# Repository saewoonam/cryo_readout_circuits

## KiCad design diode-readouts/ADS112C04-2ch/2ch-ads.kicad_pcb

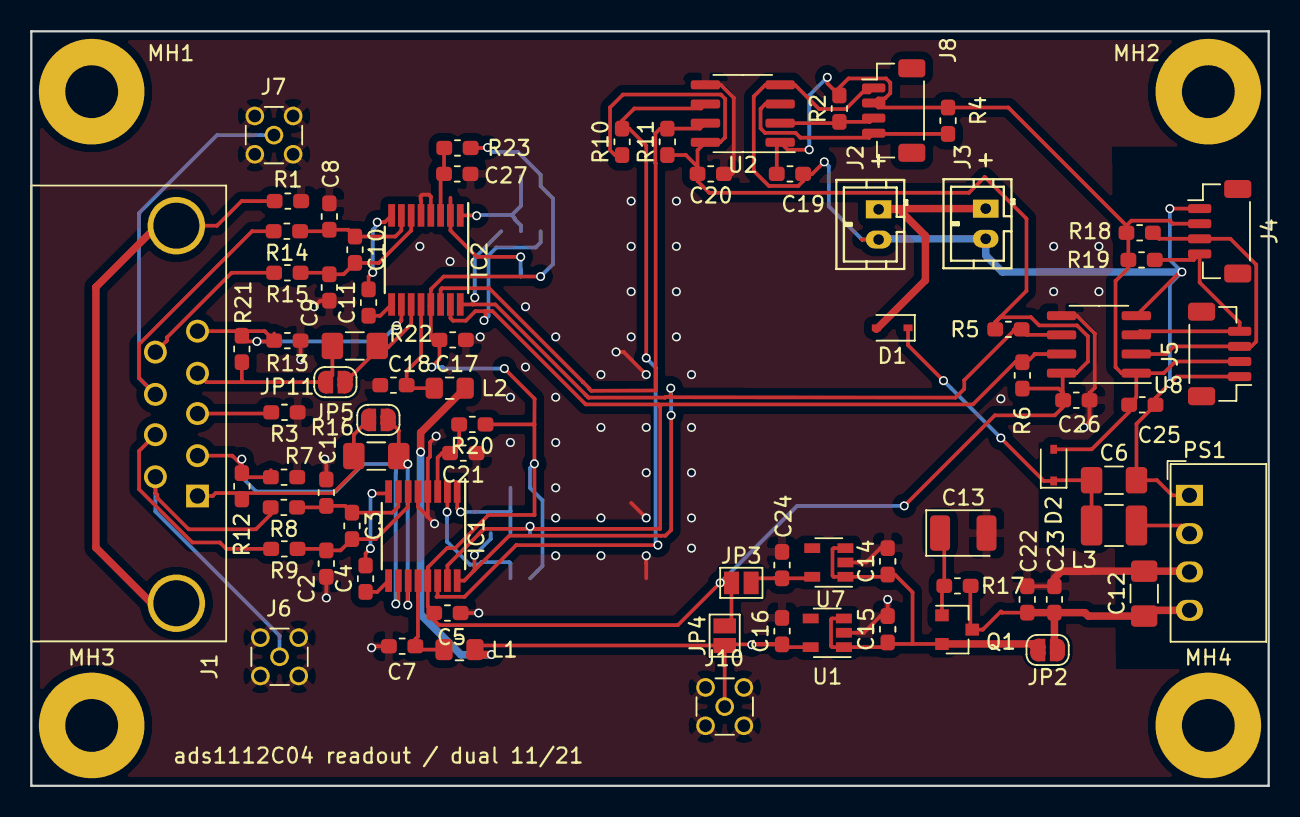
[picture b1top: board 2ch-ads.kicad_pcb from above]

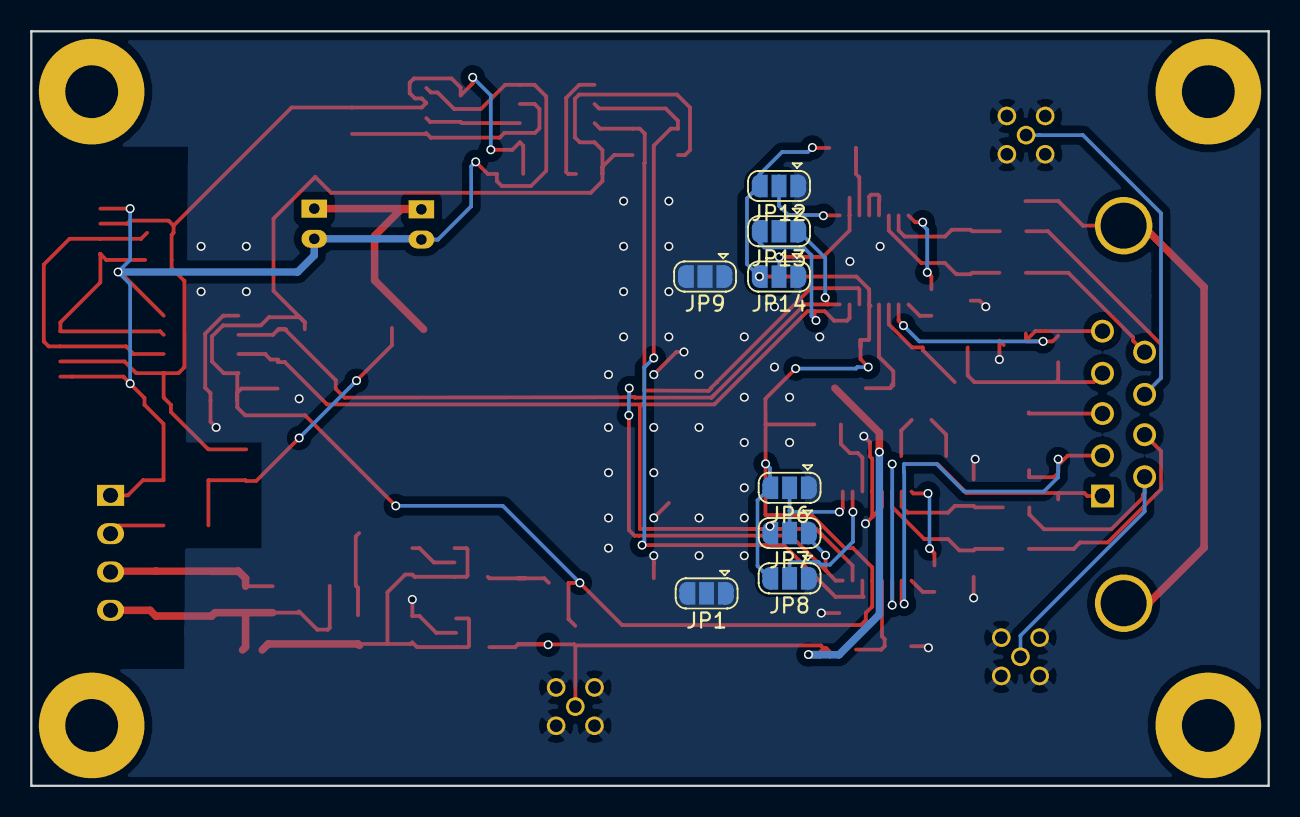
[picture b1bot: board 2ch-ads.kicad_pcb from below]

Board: 2 copper layers, 82.0 x 50.0 mm, 89 parts (8 on the bottom side), 48 nets.

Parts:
C1, C2, C4, C5, C7, C8, C9, C11, C17, C18, C19, C20, C21, C22, C25, C26, C27: 100nF; C_0603_1608Metric_Pad1.05x0.95mm_HandSolder
C3, C10, C14, C15, C16, C24: 1uF; C_0603_1608Metric_Pad1.05x0.95mm_HandSolder
C6: 4.7uF_1206_50V; C_1206_3216Metric_Pad1.42x1.75mm_HandSolder
C12: 10uF_1206_50V; C_1206_3216Metric_Pad1.42x1.75mm_HandSolder
C13: 100uF; CP_EIA-3528-12_Kemet-T
C23: 10nF; C_0603_1608Metric_Pad1.05x0.95mm_HandSolder
D1, D2: BAT60B; D_SOD-323
IC1, IC2: ADS112C04IPWR; TSSOP-16_4.4x5mm_P0.65mm
J1: DB9_Female_MountingHoles; DB9_ASSMANN
J2, J3: Conn_01x02; JST_lipo_adafruit
J4, J5, J8: A1001WV-S-04P; JST_SH_BM04B-SRSS-TB_1x04-1MP_P1.00mm_Vertical
J6, J7, J10: MMCX; MMCX_JLC
JP1, JP6, JP7, JP8, JP9, JP12, JP13, JP14: Jumper_3_Open; SolderJumper-3_P1.3mm_Open_RoundedPad1.0x1.5mm
JP2: Jumper_2_Open; SolderJumper-2_P1.3mm_Open_RoundedPad1.0x1.5mm
JP3, JP4: Jumper_NO_Small; SolderJumper-2_P1.3mm_Open_Pad1.0x1.5mm
JP5, JP11: Jumper; SolderJumper-2_P1.3mm_Open_RoundedPad1.0x1.5mm
L1, L2: MMZ2012Y202B; L_0805_2012Metric_Pad1.15x1.40mm_HandSolder
L3: 6.8uH; L_1210_3225Metric_Pad1.42x2.65mm_HandSolder
MH1, MH2, MH3, MH4: MountingHole; MountingHole_3.5mm_Pad
PS1: B0305S-1WR2; Converter_DCDC_muRata_CRE1xxxxxx3C_THT
Q1: BC847C; SOT-23
R1, R3: dnf; R_0603_1608Metric_Pad1.05x0.95mm_HandSolder
R2, R4, R5, R6, R10, R11, R18, R19: 4.7K; R_0603_1608Metric_Pad1.05x0.95mm_HandSolder
R7, R13: 10K 0.1%; R_0603_1608Metric_Pad1.05x0.95mm_HandSolder
R8, R9, R14, R15: 100K; R_0603_1608Metric_Pad1.05x0.95mm_HandSolder
R12, R21: R; R_0603_1608Metric_Pad1.05x0.95mm_HandSolder
R16, R22: 1M_0.1%; R_1206_3216Metric_Pad1.42x1.75mm_HandSolder
R17, R20, R23: 1K; R_0603_1608Metric_Pad1.05x0.95mm_HandSolder
U1, U7: LP5907MFX-3.3; SOT-23-5
U2: ADUM1250; SOIC-8_3.9x4.9mm_P1.27mm
U8: ISO1541; SOIC-8_3.9x4.9mm_P1.27mm

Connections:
/Channel0/A0: IC1.1, JP6.2, JP7.2
/Channel0/A1: IC1.2, JP1.2, JP8.2
/Channel0/AIN0: IC1.11, JP5.2, R16.1
/Channel0/I+: J1.1, JP5.1, R12.1, R16.2
/Channel0/I-: IC1.10, J1.2, R7.1, R12.2
/Channel0/V+: J1.6, J6.1, R8.2
/Channel0/V-: J1.7, R9.2
/Channel0/Vpower: C7.2, IC1.12, L1.2
/Channel1/A0: IC2.1, JP12.2, JP13.2
/Channel1/A1: IC2.2, JP9.2, JP14.2
/Channel1/AIN0: IC2.11, JP11.2, R22.1
/Channel1/I+: J1.4, JP11.1, R21.1, R22.2
/Channel1/I-: IC2.10, J1.5, R13.1, R21.2
/Channel1/V+: J1.8, J7.1, R14.2
/Channel1/V-: J1.9, R15.2
/Channel1/Vpower: C18.2, IC2.12, L2.2
/Sheet605654E7/i2c_power: C6.1, D1.1, D2.1, L3.2
/Sheet6128984A/gpio0: IC1.14, R10.2, U2.6
/Sheet6128984A/gpio1: IC2.14, R11.2, U2.7
/analog: C16.1, J10.1, JP4.1, L1.1, L2.1, U1.5
/scl: IC1.16, IC2.16, JP1.1, JP7.1, JP9.1, JP13.1, R5.2, U8.6
/sda: IC1.15, IC2.15, JP1.3, JP7.3, JP9.3, JP13.3, R6.2, U8.7
GND: C1.1, C2.2, C5.2, C7.1, C8.1, C9.2, C12.2, C13.2, C14.2, C15.2, C16.2, C17.2, C18.1, C20.1, C21.1, C22.1, C23.1, C24.2, C26.1, C27.1, IC1.4, IC1.5, IC2.4, IC2.5, J6.2, J7.2, J10.2, JP6.1, JP8.1, JP12.1, JP14.1, PS1.3, R1.2, R3.1, R7.2, R13.2, U1.2, U2.5, U7.2, U8.5
GNDPWR: C6.2, C19.2, C25.2, J2.2, J3.2, J4.1, J5.1, J8.1, PS1.1, U2.4, U8.4
unnamed: C1.2, C3.1, IC1.7, R8.1
unnamed: C2.1, C3.2, IC1.6, R9.1
unnamed: C4.1, IC1.9
unnamed: C4.2, IC1.8
unnamed: C8.2, C10.1, IC2.7, R14.1
unnamed: C9.1, C10.2, IC2.6, R15.1
unnamed: C11.1, IC2.9
unnamed: C11.2, IC2.8
unnamed: C12.1, C22.2, C23.2, JP2.1, PS1.4, Q1.3, R17.1
unnamed: C13.1, Q1.1, R17.2
unnamed: C14.1, C15.1, JP2.2, Q1.2, U1.1, U1.3, U7.1, U7.3
unnamed: C21.2, IC1.3, R20.2
unnamed: C24.1, JP3.2, U7.5
unnamed: C27.2, IC2.3, R23.2
unnamed: D1.2, J2.1, J3.1
unnamed: J1.0, R1.1
unnamed: J1.3, R3.2
unnamed: J4.3, J5.3, R18.1, U8.2
unnamed: J4.4, J5.4, R19.1, U8.3
unnamed: J8.3, R2.1, U2.2
unnamed: J8.4, R4.1, U2.3
unnamed: L3.1, PS1.2
VCC: C19.1, C25.1, D2.2, J4.2, J5.2, J8.2, R2.2, R4.2, R18.2, R19.2, U2.1, U8.1
VD: C5.1, C17.1, C20.2, C26.2, IC1.13, IC2.13, JP3.1, JP4.2, JP6.3, JP8.3, JP12.3, JP14.3, R5.1, R6.1, R10.1, R11.1, R20.1, R23.1, U2.8, U8.8

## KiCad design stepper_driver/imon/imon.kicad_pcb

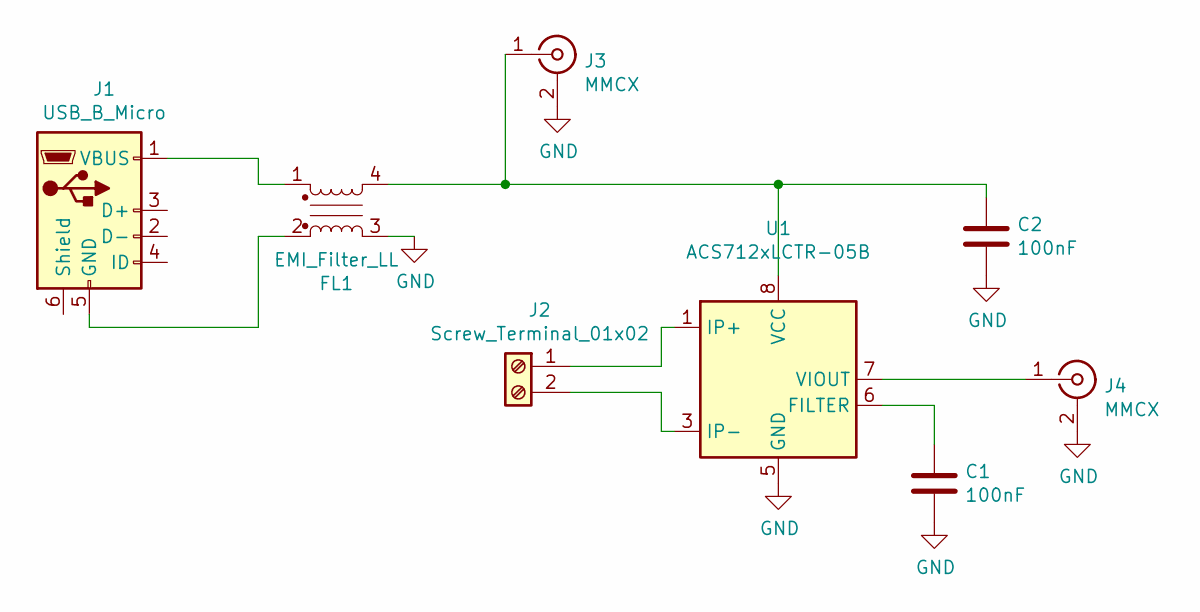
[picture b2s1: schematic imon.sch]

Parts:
C1, C2: 100nF; C_0603_1608Metric_Pad1.05x0.95mm_HandSolder; MPN CC0603KRX7R9BB104; LCSC C14663
FL1: EMI_Filter_LL; L_CommonMode_Wuerth_WE-SL2; LCSC C261397
J1: USB_B_Micro; USB_Micro-B_Molex-105017-0001; LCSC C505111
J2: Screw_Terminal_01x02; TerminalBlock_Phoenix_MKDS-1,5-2-5.08_1x02_P5.08mm_Horizont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; MPN WJ500V-5.08-2P; LCSC C8465
J3, J4: MMCX; MMCX_JLC; MPN KH-MMCX-Z; LCSC C530664
U1: ACS712xLCTR-05B; SOIC-8_3.9x4.9mm_P1.27mm; MPN ACS712ELCTR-05B-T; LCSC C44471

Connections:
GND: C1.2, C2.2, FL1.3, J3.2 (Ext), J4.2 (Ext), U1.5 (GND)
unnamed: C1.1, U1.6 (FILTER)
unnamed: C2.1, FL1.4, J3.1 (In), U1.8 (VCC)
unnamed: FL1.1, J1.1 (VBUS)
unnamed: FL1.2, J1.5 (GND)
unnamed: J2.1, U1.1 (IP+), U1.2 (IP+)
unnamed: J2.2, U1.3 (IP-), U1.4 (IP-)
unnamed: J4.1 (In), U1.7 (VIOUT)

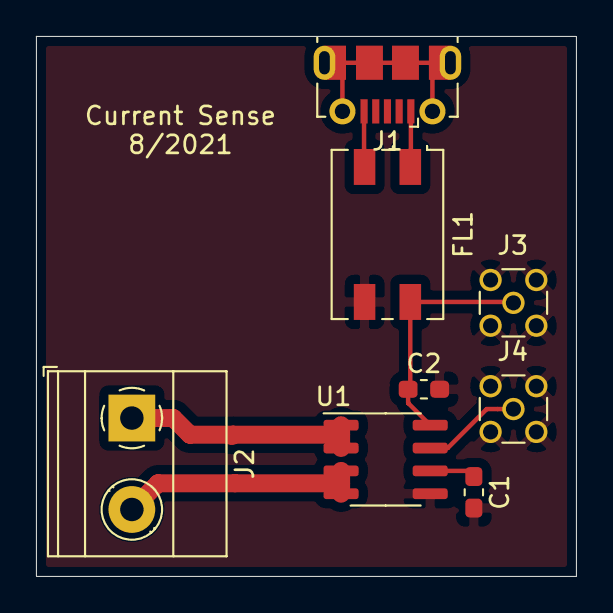
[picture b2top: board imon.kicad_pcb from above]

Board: 2 copper layers, 30.0 x 30.0 mm, 8 parts (0 on the bottom side), 8 nets.

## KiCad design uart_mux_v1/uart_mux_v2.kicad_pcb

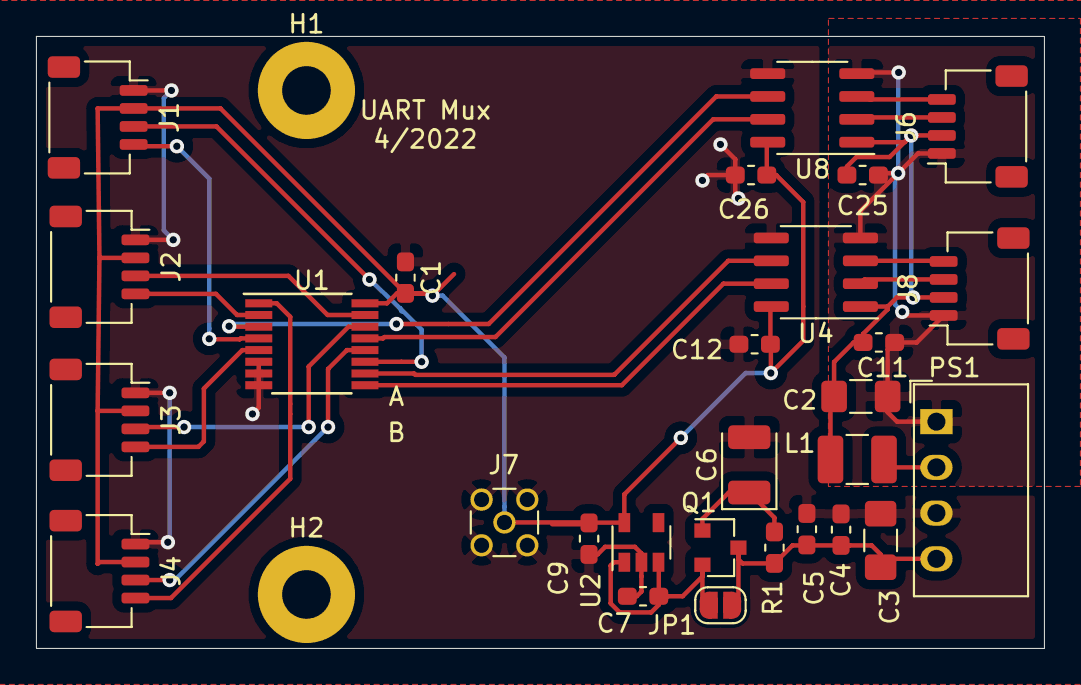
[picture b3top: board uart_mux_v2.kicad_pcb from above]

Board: 2 copper layers, 56.0 x 34.0 mm, 30 parts (0 on the bottom side), 24 nets.

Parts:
C1, C4, C11, C12, C25, C26: 100nF; C_0603_1608Metric_Pad1.05x0.95mm_HandSolder
C2: 4.7uF_1206_50V; C_1206_3216Metric_Pad1.42x1.75mm_HandSolder
C3: 10uF_1206_50V; C_1206_3216Metric_Pad1.42x1.75mm_HandSolder
C5: 10nF; C_0603_1608Metric_Pad1.05x0.95mm_HandSolder
C6: 100uF; CP_EIA-3528-12_Kemet-T
C7, C9: 1uF; C_0603_1608Metric_Pad1.05x0.95mm_HandSolder
H1, H2: MountingHole; MountingHole_2.7mm_M2.5_Pad
J1, J2, J3, J4, J6, J8: JST_SH_Conn_01x04_i2c_horizontal; JST_SH_SM04B-SRSS-TB_1x04-1MP_P1.00mm_Horizontal
J7: MMCX; MMCX_JLC
JP1: Jumper_2_Open; SolderJumper-2_P1.3mm_Open_RoundedPad1.0x1.5mm
L1: 6.8uH; L_1210_3225Metric_Pad1.42x2.65mm_HandSolder
PS1: B0305S-1WR2; Converter_DCDC_muRata_CRE1xxxxxx3C_THT
Q1: BC847C; SOT-23
R1: 1K; R_0603_1608Metric_Pad1.05x0.95mm_HandSolder
U1: 4052; TSSOP-16_4.4x5mm_P0.65mm
U2: LP5907MFX-3.3; SOT-23-5
U4, U8: ISO1541; SOIC-8_3.9x4.9mm_P1.27mm

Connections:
/A: U1.10, U4.6
/B: U1.9, U4.7
/Sheet626DA5AD/A_in: J8.4, U4.3
/Sheet626DA5AD/B_in: J8.3, U4.2
/Sheet626DA5AD/scl: U1.3, U8.6
/Sheet626DA5AD/scl_in: J6.4, U8.3
/Sheet626DA5AD/sda: U1.13, U8.7
/Sheet626DA5AD/sda_in: J6.3, U8.2
GND: C1.1, C3.2, C4.1, C5.1, C6.2, C7.2, C9.2, C12.1, C26.1, J1.1, J2.1, J3.1, J4.1, J7.2, PS1.3, U1.6, U1.7, U1.8, U2.2, U4.5, U8.5
GNDPWR: C2.2, C11.2, C25.2, J6.1, J8.1, PS1.1, U4.4, U8.4
unnamed: C3.1, C4.2, C5.2, JP1.1, PS1.4, Q1.3, R1.1
unnamed: C6.1, Q1.1, R1.2
unnamed: C7.1, JP1.2, Q1.2, U2.1, U2.3
unnamed: J1.3, U1.11
unnamed: J1.4, U1.4
unnamed: J2.3, U1.15
unnamed: J2.4, U1.2
unnamed: J3.3, U1.14
unnamed: J3.4, U1.5
unnamed: J4.3, U1.12
unnamed: J4.4, U1.1
unnamed: L1.1, PS1.2
VCC: C1.2, C9.1, C12.2, C26.2, J1.2, J2.2, J3.2, J4.2, J7.1, U1.16, U2.5, U4.8, U8.8
VD: C2.1, C11.1, C25.1, J6.2, J8.2, L1.2, U4.1, U8.1
